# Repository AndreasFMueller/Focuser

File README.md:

# Focuser

The motor focus driver from starizona is quite feature complete,
more so than many other devices, but it is very large and heavy.
Also it is not possible to actuate the focuser without grabbing
the device, a wireless solution would be preferable. The present
project solves this problem.

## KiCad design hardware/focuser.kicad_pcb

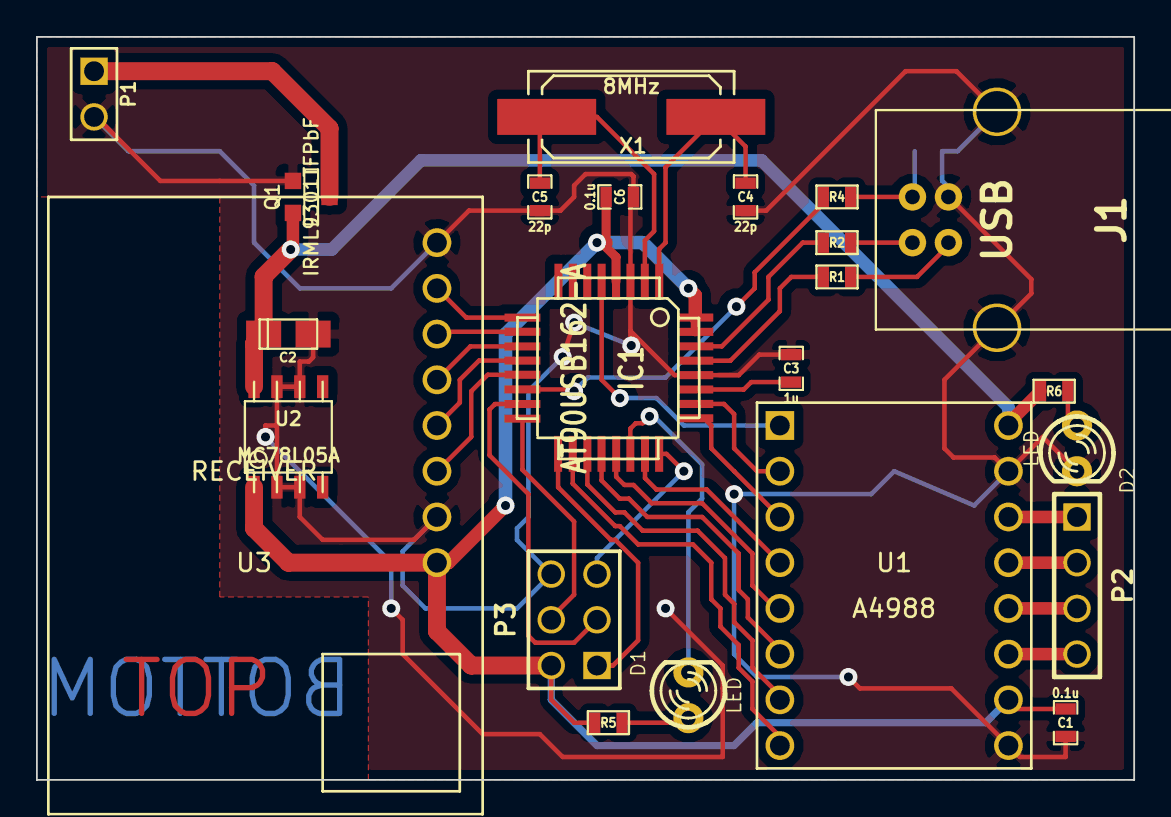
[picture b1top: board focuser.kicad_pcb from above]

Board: 2 copper layers, 61.0 x 41.3 mm, 24 parts (1 on the bottom side), 37 nets.

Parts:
C1, C6: 0.1u; SM0603_Capa
C2: 0.33u; c_tant_A
C3: 1u; SM0603_Capa
C4, C5: 22p; SM0603_Capa
D1, D2: LED; LED-3MM
IC1: AT90USB162-A; TQFP32
J1: USB; USB_B
P1: Power; PIN_ARRAY_2X1
P2: Motor; PIN_ARRAY_4x1
P3: ISP; pin_array_3x2
Q1: IRML9301TFPbF; SOT23GDS
R1, R2: 22; SM0603
R3: 220k; SM0603
R4: 1k; SM0603
R5: 610; SM0603
R6: 2k; SM0603
U1: A4988
U2: MC78L05A; so-8
U3: RECEIVER; Receiver
X1: 8MHz; Q_49U3HMS

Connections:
+5V: C1.1, C6.1, IC1.4, IC1.31, IC1.32, P3.2, R5.2, U1.10, U2.1, U3.1
+12V: C2.1, Q1.S, R6.1, U1.16, U2.8
GND: C1.2, C2.2, C3.2, C4.1, C5.1, C6.2, D2.2, IC1.3, IC1.28, J1.4, J1.5, J1.6, P1.2, P3.6, Q1.G, R3.2, U1.9, U1.15, U2.2, U2.3, U2.6, U2.7, U3.2, U3.8
unnamed: C4.2, IC1.1, X1.1
unnamed: C5.2, IC1.2, X1.2
unnamed: IC1.30, R2.2
unnamed: IC1.29, R1.2
unnamed: IC1.16, P3.4
unnamed: IC1.24, P3.5
unnamed: IC1.15, P3.3
unnamed: IC1.17, P3.1
unnamed: D1.2, IC1.22
unnamed: D2.1, R6.2
unnamed: D1.1, R5.1
unnamed: P2.4, U1.11
unnamed: P2.3, U1.12
unnamed: P2.2, U1.13
unnamed: P2.1, U1.14
unnamed: P1.1, Q1.D
unnamed: IC1.13, U3.3
unnamed: IC1.12, U3.4
unnamed: IC1.11, U3.5
unnamed: IC1.10, U3.6
unnamed: IC1.9, U3.7
unnamed: IC1.25, U1.3
unnamed: IC1.26, U1.2
unnamed: IC1.23, U1.4
unnamed: IC1.5, U1.1
unnamed: C3.1, IC1.27
unnamed: IC1.14, R4.1
unnamed: J1.1, R3.1, R4.2
unnamed: IC1.18, U1.8
unnamed: IC1.19, U1.7
unnamed: IC1.20, U1.6
unnamed: IC1.21, U1.5
unnamed: J1.3, R1.1
unnamed: J1.2, R2.1

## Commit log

2016-01-16 add focuser schematics and layout
2016-01-25 make manufacturable boards (according to Eurocircuit's rules)
2016-01-25 add files for firmware
2016-01-25 get it to compile ;-)
2016-02-07 add missing file focuser.lib
2016-02-10 complete the firmware for the focuser
2016-02-10 remove led_on from motor_save
2016-02-10 fix client bug
2016-02-10 typo
2016-02-11 add serial command
2016-05-17 fix some minor bugs
2016-05-31 use microstepping for slow speed
2016-05-31 fix position counter for microstepping
2016-06-02 new version number
2016-06-02 add focuser case to repo
2017-07-31 extend focuser range
2018-04-27 minor update
2018-05-01 move eeprom stuff to a separate file
2018-05-01 add missing LUFAConfig.h
2018-05-01 changes for new LUFA
2018-05-01 add datasheet
2018-05-01 convert to polling
2019-09-06 top speed, automatic serial
2019-09-06 add missing file
